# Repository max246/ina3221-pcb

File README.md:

# INA3221 PCB 

This is an opensource PCB which I provide to everyone who will need to implement on their project or just to have a hack for it.

My skills on PCB are not that great so you might find some odd routing but you can adjust that by yourself from the schematic.

The Shut resistor is a 0.1 ohm 2512 at 2W, that gaves me a good result on the reading.

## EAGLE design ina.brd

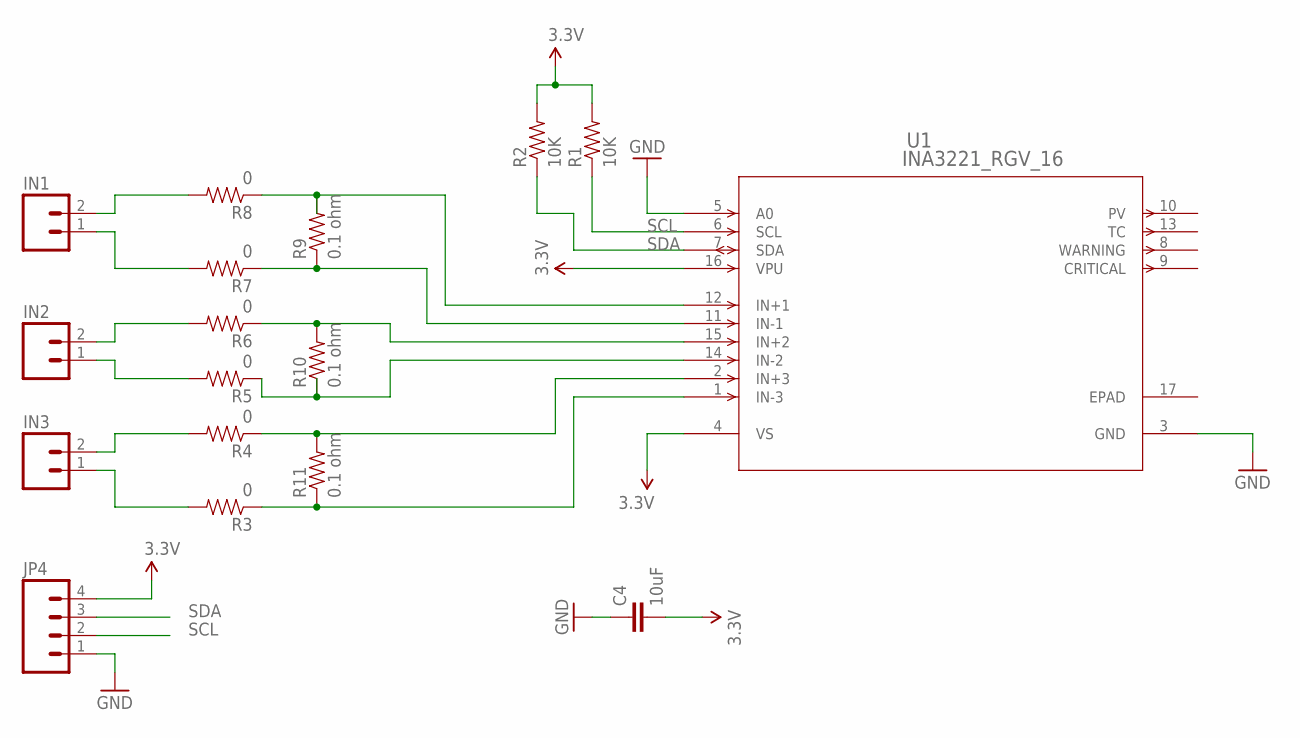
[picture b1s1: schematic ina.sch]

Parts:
C4: 10uF; 1206; MPN 1206B106K160CT
IN1, IN2, IN3: M02PTH; 1X02
JP4: M04LONGPADS; 1X04_LONGPADS
R1, R2: 10K; 1206; MPN RC1206FR-0710KL
R3, R4, R5, R6, R7, R8: 0; 1206; MPN WCR1206-R005JI
R9, R10, R11: 0.1 ohm; R2512; MPN CRM2512-JX-R100ELF
U1: INA3221_RGV_16; RGV16_2P16X2P16; MPN INA3221AIRGVT

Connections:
3.3V: C4.2, JP4.4, R1.2, R2.2, U1.4 (VS), U1.16 (VPU)
GND: C4.1, JP4.1, U1.3 (GND), U1.5 (A0)
IN1_N: R7.1, R9.1, U1.11 (IN-1)
IN1_P: R8.1, R9.2, U1.12 (IN+1)
IN2_N: R5.1, R10.1, U1.14 (IN-2)
IN2_P: R6.1, R10.2, U1.15 (IN+2)
IN3_N: R3.1, R11.1, U1.1 (IN-3)
IN3_P: R4.1, R11.2, U1.2 (IN+3)
unnamed: IN1.2, R8.2
unnamed: IN1.1, R7.2
unnamed: IN2.2, R6.2
unnamed: IN2.1, R5.2
unnamed: IN3.2, R4.2
unnamed: IN3.1, R3.2
SCL: JP4.2, R1.1, U1.6 (SCL)
SDA: JP4.3, R2.1, U1.7 (SDA)

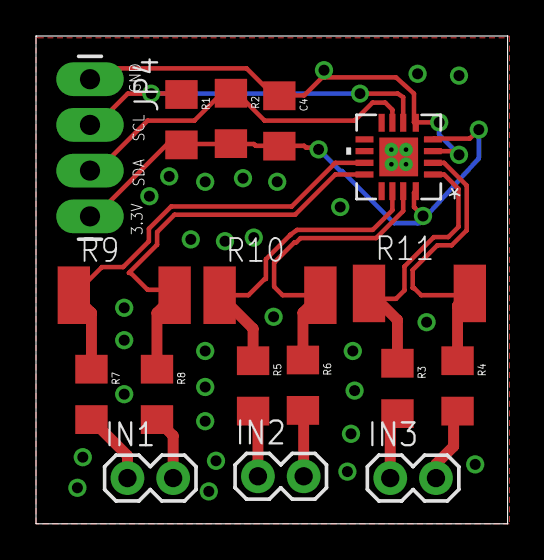
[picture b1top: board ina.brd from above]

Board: 2 copper layers, 26.2 x 27.1 mm, 17 parts (0 on the bottom side), 16 nets.

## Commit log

2016-11-26 INA3221 board and lib
2016-11-26 add preview

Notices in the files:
parts and their libraries:
SparkFun-Passives: Licensing: Creative Commons ShareAlike 4.0 International - https://creativecommons.org/licenses/by-sa/4.0
